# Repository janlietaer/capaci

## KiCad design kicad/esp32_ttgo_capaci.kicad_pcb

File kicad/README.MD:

# This is a KiCad library for TTGO_T_Display.
You need add "TTGO_T_Display.kicad_sym" as symbol library with name TTGO_T_Display to KiCad.
This file is in folder "symbols".
Also you need to add "TTGO_T_Display.pretty" folder as footprint library with name TTGO_T_Display to KiCad.
This folder is in folder footprints.

Library created by WolodiaM

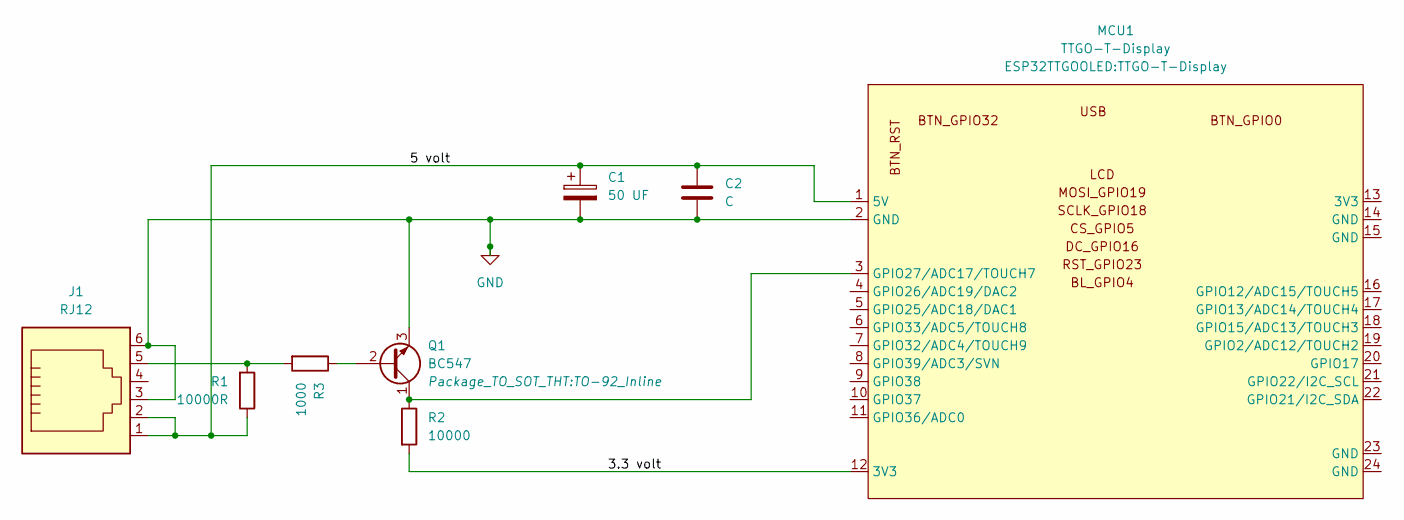
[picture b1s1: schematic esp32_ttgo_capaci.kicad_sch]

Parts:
C1: 50 UF; CP_Radial_D8.0mm_P2.50mm
C2: C; C_Disc_D3.0mm_W1.6mm_P2.50mm
J1: RJ12; RJ12_Amphenol_54601
MCU1: TTGO-T-Display
Q1: BC547; TO-92_Inline
R1: 10000R; R_Axial_DIN0309_L9.0mm_D3.2mm_P12.70mm_Horizontal
R2: 10000; R_Axial_DIN0309_L9.0mm_D3.2mm_P12.70mm_Horizontal
R3: 1000; R_Axial_DIN0309_L9.0mm_D3.2mm_P12.70mm_Horizontal

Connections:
/3.3 volt: MCU1.12 (3V3), R2.2
/5 volt: C1.1, C2.1, J1.1, J1.2, MCU1.1 (5V), R1.1
GND: C1.2, C2.2, J1.3, J1.6, MCU1.2 (GND), Q1.3 (E)
unnamed: J1.5, R1.2, R3.2
unnamed: MCU1.3 (GPIO27/ADC17/TOUCH7), Q1.1 (C), R2.1
unnamed: Q1.2 (B), R3.1

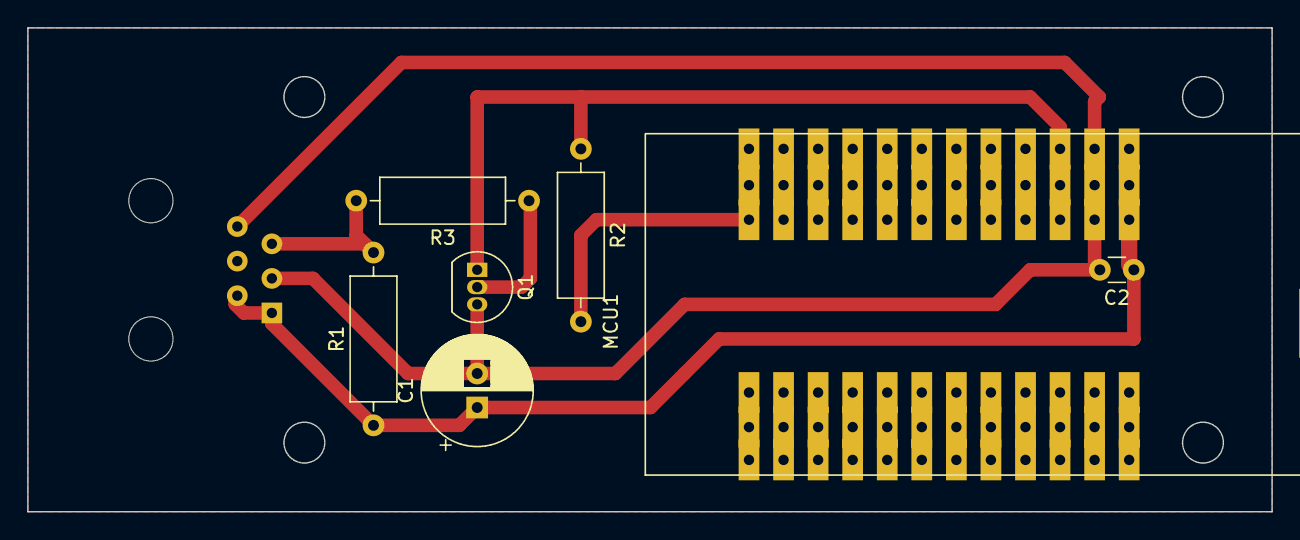
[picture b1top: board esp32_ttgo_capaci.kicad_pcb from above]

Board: 2 copper layers, 91.4 x 35.6 mm, 8 parts (1 on the bottom side), 6 nets.

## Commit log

2022-03-05 main op juiste plaats
2022-03-05 type
2022-03-05 huidig verbruik kan negatief zijn (pv)
2022-03-05 layout
2022-03-05 typo
2022-03-06 futje
2022-03-08 bugje string
2022-03-08 bugjes
2022-03-12 heel eenvoudig zonder functie en met een verkeerd gebrukte var eruit
2022-03-15 bug + opruilmen
2022-03-17 reportoing
2022-03-20 debugging piet
2022-03-25 commentaar
2022-11-08 opkuis
2022-11-08 lib in src
2022-11-08 met zcherm erbij
2022-11-11 EXTRA INFO OP SCHERM + MAAND KARTIER RESET OMDRAAIEN
2022-11-11 rare commit
2022-11-15 met schema
2022-11-17 extra docu
2022-11-24 kicad erbij
2022-12-13 dddddddd
2022-12-19 dddd
2022-12-19 erbij
